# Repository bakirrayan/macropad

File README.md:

# macropad

## Composition
- 16 key switchs
- 1 oled screen 0.96
- 2 rotary encoders

## PCB
PCB files can be found in "macro" folder along with the zip file to order it from pcbway

## Code
### Installation process
- Copy /pico_files/adafruit-circuitpython-raspberry_pi_pico-fr-8.0.4 to your Rpi pico 
- After a few seconds your pico will restart and a disk named circuitpython will show up
- Copy /pico_files/kmk /pico_files/lib /pico_files/code.py /pico_files/boot.py /pico_files/oled.py to the circuitpython disk
- The keyboard should work instatly

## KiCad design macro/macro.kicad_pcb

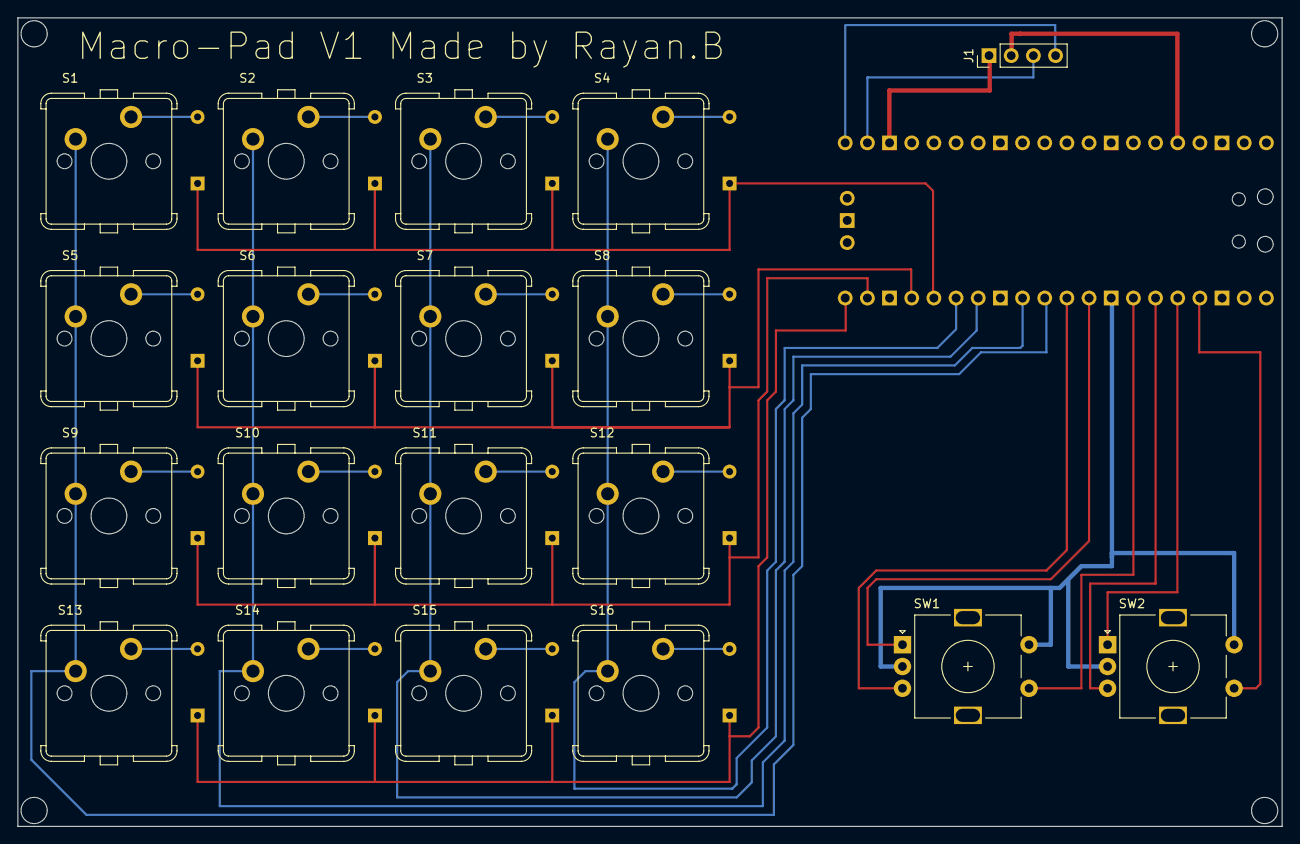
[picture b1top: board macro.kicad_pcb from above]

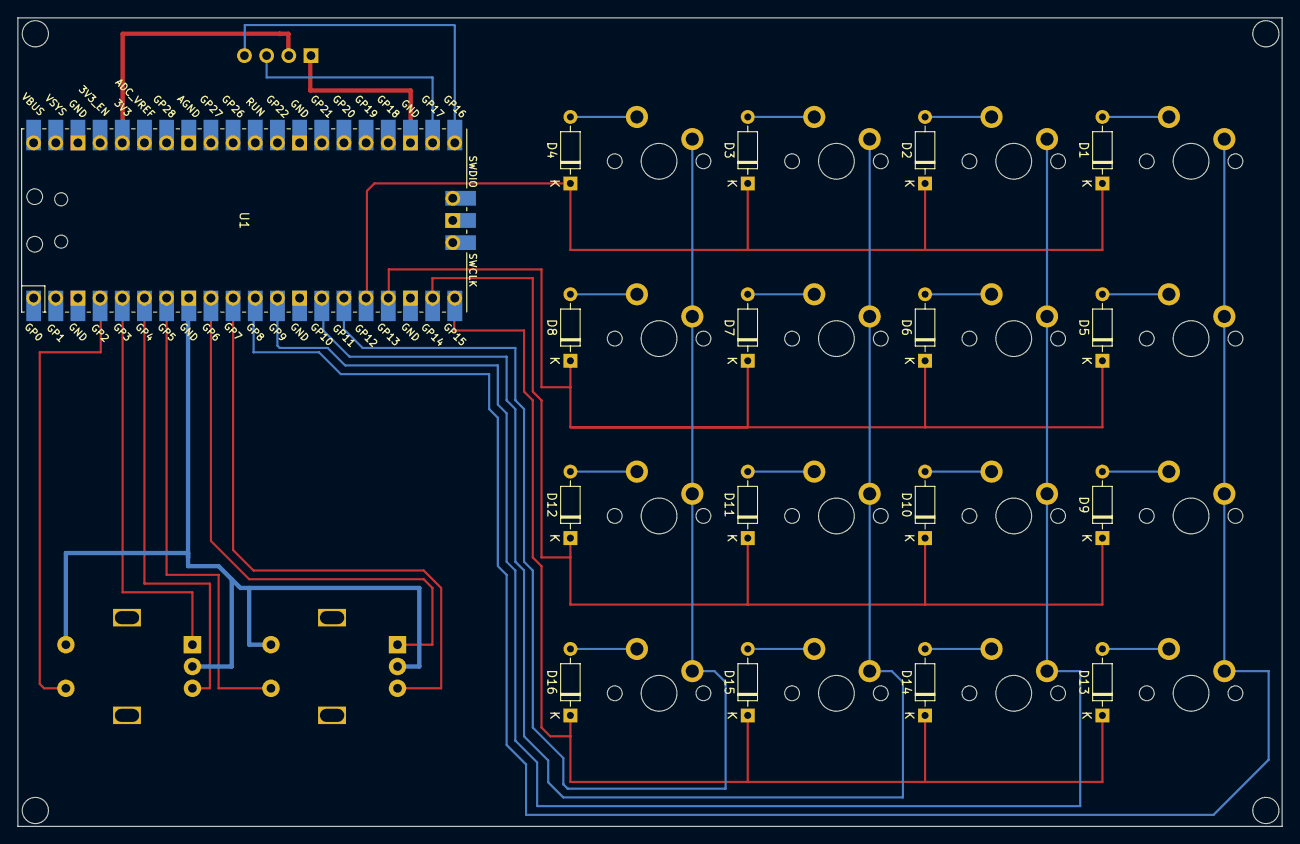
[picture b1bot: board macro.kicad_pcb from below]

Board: 2 copper layers, 144.9 x 92.6 mm, 36 parts (17 on the bottom side), 35 nets.

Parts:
D1, D2, D3, D4, D5, D6, D7, D8, D9, D10, D11, D12, D13, D14, D15, D16: 1N4148; D_DO-35_SOD27_P7.62mm_Horizontal
J1: Conn_01x04_Socket; PinHeader_1x04_P2.54mm_Vertical
S1, S2, S3, S4, S5, S6, S7, S8, S9, S10, S11, S12, S13, S14, S15, S16: CHERRY_CHERRY_MX
SW1, SW2: RotaryEncoder_Switch; RotaryEncoder_Alps_EC11E-Switch_Vertical_H20mm
U1: Pico; RPi_Pico_SMD_TH

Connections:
/c1: SW1.S1, U1.7 (GPIO5)
/c21: SW2.S1, U1.4 (GPIO2)
/col1: S1.S1, S5.S1, S9.S1, S13.S1, U1.11 (GPIO8)
/col2: S2.S1, S6.S1, S10.S1, S14.S1, U1.12 (GPIO9)
/col3: S3.S1, S7.S1, S11.S1, S15.S1, U1.14 (GPIO10)
/col4: S4.S1, S8.S1, S12.S1, S16.S1, U1.15 (GPIO11)
/gn: SW1.C, SW1.S2, SW2.C, SW2.S2, U1.8 (GND)
/gn2: J1.1, U1.23 (GND)
/r1a: SW1.A, U1.9 (GPIO6)
/r1b: SW1.B, U1.10 (GPIO7)
/r2a: SW2.A, U1.5 (GPIO3)
/r2b: SW2.B, U1.6 (GPIO4)
/raw1: D1.1 (K), D2.1 (K), D3.1 (K), D4.1 (K), U1.16 (GPIO12)
/raw2: D5.1 (K), D6.1 (K), D7.1 (K), D8.1 (K), U1.17 (GPIO13)
/raw3: D9.1 (K), D10.1 (K), D11.1 (K), D12.1 (K), U1.19 (GPIO14)
/raw4: D13.1 (K), D14.1 (K), D15.1 (K), D16.1 (K), U1.20 (GPIO15)
/scl: J1.3, U1.22 (GPIO17)
/sda: J1.4, U1.21 (GPIO16)
/vcc: J1.2, U1.36 (3V3)
unnamed: D1.2 (A), S1.S2
unnamed: D2.2 (A), S2.S2
unnamed: D3.2 (A), S3.S2
unnamed: D4.2 (A), S4.S2
unnamed: D5.2 (A), S5.S2
unnamed: D6.2 (A), S6.S2
unnamed: D7.2 (A), S7.S2
unnamed: D8.2 (A), S8.S2
unnamed: D9.2 (A), S9.S2
unnamed: D10.2 (A), S10.S2
unnamed: D11.2 (A), S11.S2
unnamed: D12.2 (A), S12.S2
unnamed: D13.2 (A), S13.S2
unnamed: D14.2 (A), S14.S2
unnamed: D15.2 (A), S15.S2
unnamed: D16.2 (A), S16.S2

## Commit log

2023-02-26 some changes on the pcb
2023-02-26 some changes on the gerbers files
2023-03-11 code changes
2023-03-25 adding support for oled and layers
2023-03-25 changing layer layout
2023-03-25 readme cjanges
